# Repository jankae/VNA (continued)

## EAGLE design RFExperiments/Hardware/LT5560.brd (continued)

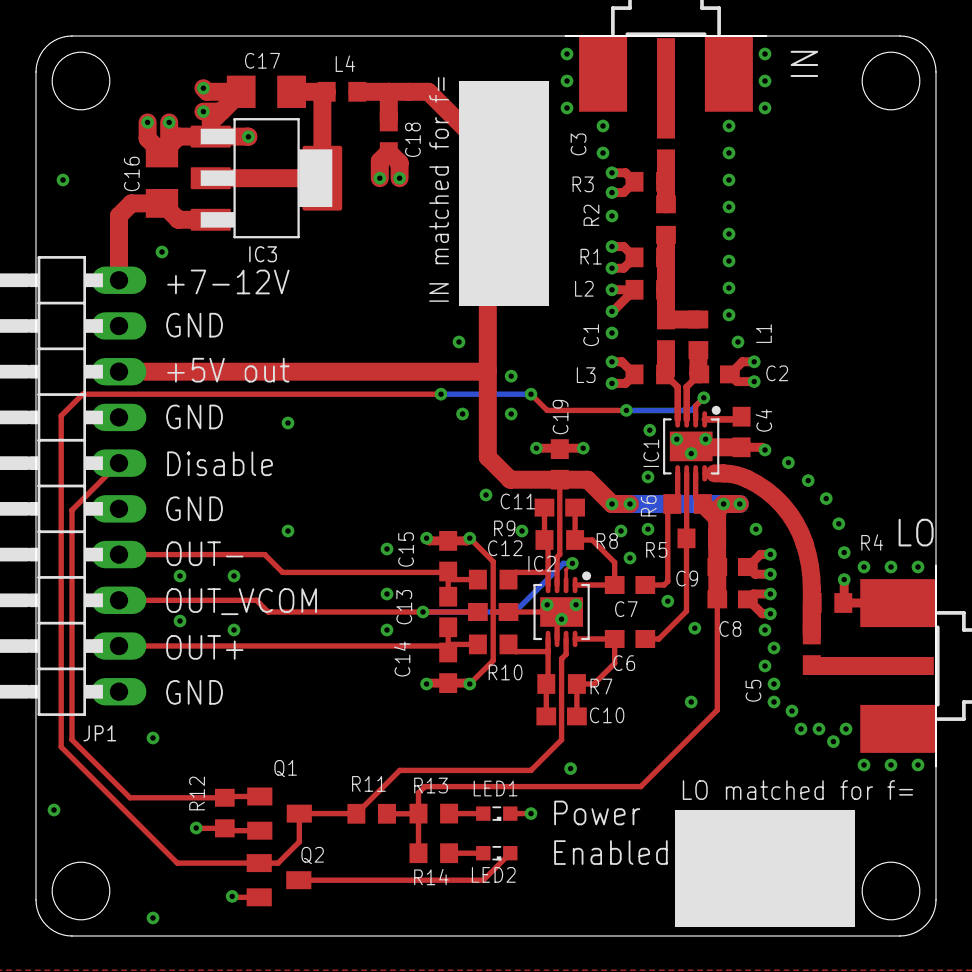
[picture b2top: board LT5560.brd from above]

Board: 2 copper layers, 50.0 x 50.0 mm, 47 parts (0 on the bottom side), 26 nets.

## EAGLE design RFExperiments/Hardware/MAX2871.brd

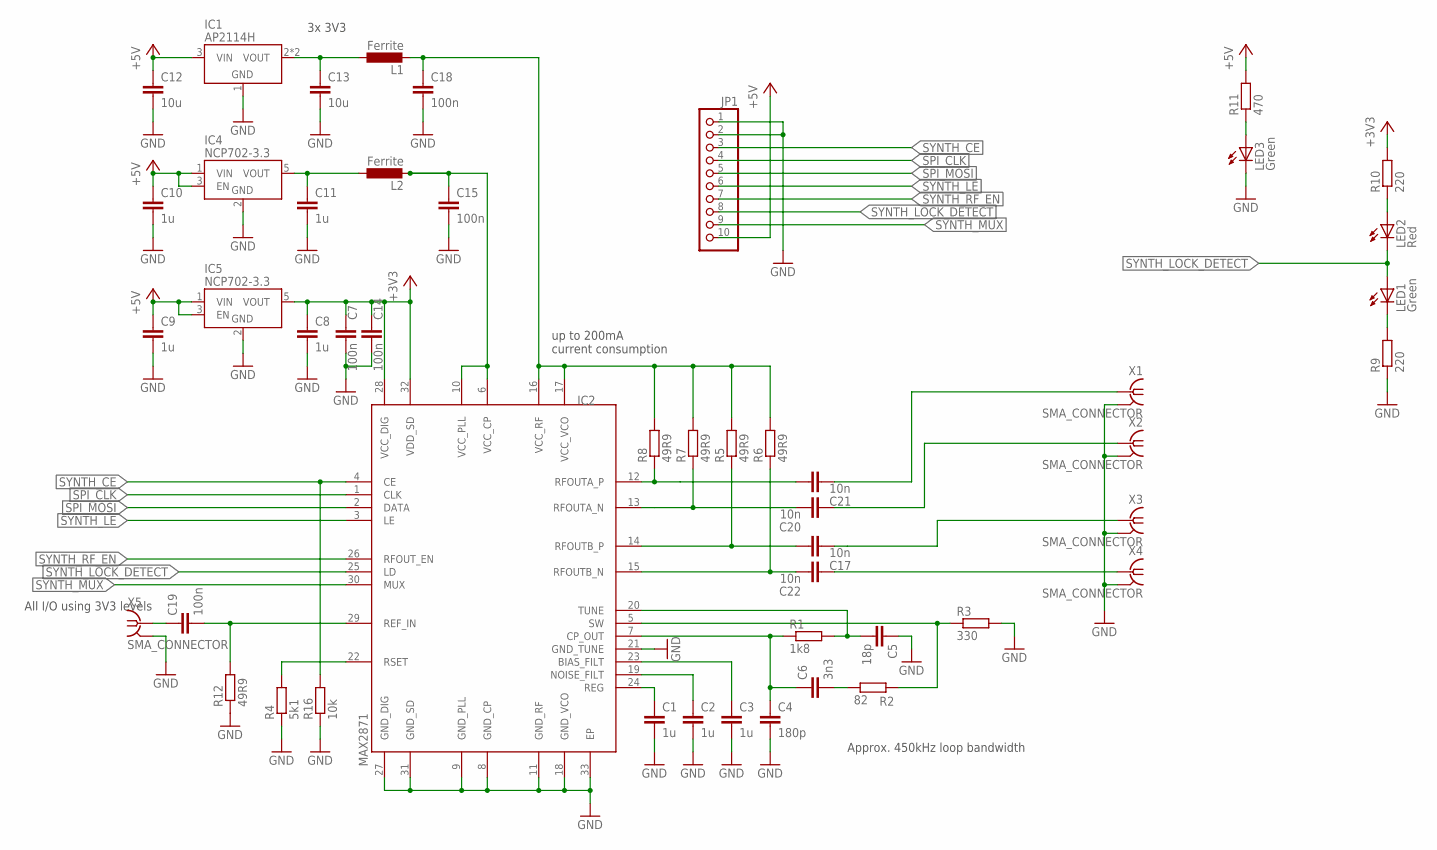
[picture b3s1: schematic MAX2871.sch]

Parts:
C1, C2, C3, C8, C9, C10, C11: 1u; C0603
C4: 180p; C0603
C5: 18p; C0603
C6: 3n3; C0603
C7, C14, C15, C18, C19: 100n; C0603
C12, C13: 10u; C1206
C17, C20, C21, C22: 10n; C0603
IC1: AP2114H; SOT230P700X180-4
IC2: MAX2871; QFN50P500X500X80-33T310
IC4, IC5: NCP702-3.3; SOT95P240X110-5
JP1: PINHD-1X10/90; 1X10/90
L1, L2: Ferrite; R0603
LED1, LED3: Green; LED_SML0603
LED2: Red; LED_SML0603
R1: 1k8; R0603
R2: 82; R0603
R3: 330; R0603
R4: 5k1; R0603
R5, R6, R7, R8, R12: 49R9; R0603
R9, R10: 220; R0603
R11: 470; R0603
R16: 10k; R0603
X1, X2, X3, X4, X5: SMA_CONNECTOR; J502-ND-142-0711-821/826

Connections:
10MHZ_REF: C19.1, X5.1
+3V3: C7.1, C8.1, C14.1, IC2.28 (VCC_DIG), IC2.32 (VDD_SD), IC5.5 (VOUT), R10.2
+5V: C9.1, C10.1, C12.1, IC1.3 (VIN), IC4.1 (VIN), IC4.3 (EN), IC5.1 (VIN), IC5.3 (EN), JP1.10, R11.2
GND: C1.2, C2.2, C3.2, C4.2, C5.1, C7.2, C8.2, C9.2, C10.2, C11.2, C12.2, C13.2, C14.2, C15.2, C18.2, IC1.1 (GND), IC2.8 (GND_CP), IC2.9 (GND_PLL), IC2.11 (GND_RF), IC2.18 (GND_VCO), IC2.21 (GND_TUNE), IC2.27 (GND_DIG), IC2.31 (GND_SD), IC2.33 (EP), IC4.2 (GND), IC5.2 (GND), JP1.1, JP1.2, LED3.C, R3.2, R4.1, R9.1, R12.1, R16.1, X1.G@1 (2), X1.G@2 (2), X1.G@3 (2), X1.G@4 (2), X2.G@1 (2), X2.G@2 (2), X2.G@3 (2), X2.G@4 (2), X3.G@1 (2), X3.G@2 (2), X3.G@3 (2), X3.G@4 (2), X4.G@1 (2), X4.G@2 (2), X4.G@3 (2), X4.G@4 (2), X5.G@1 (2), X5.G@2 (2), X5.G@3 (2), X5.G@4 (2)
unnamed: C5.2, IC2.20 (TUNE), R1.2
unnamed: C4.1, C6.1, IC2.7 (CP_OUT), R1.1
unnamed: C1.1, IC2.24 (REG)
unnamed: C2.1, IC2.19 (NOISE_FILT)
unnamed: C3.1, IC2.23 (BIAS_FILT)
unnamed: C6.2, R2.1
unnamed: IC2.5 (SW), R2.2, R3.1
unnamed: IC2.22 (RSET), R4.2
unnamed: C19.2, IC2.29 (REF_IN), R12.2
unnamed: C18.1, IC2.16 (VCC_RF), IC2.17 (VCC_VCO), L1.2, R5.2, R6.2, R7.2, R8.2
unnamed: C15.1, IC2.6 (VCC_CP), IC2.10 (VCC_PLL), L2.2
unnamed: C22.2, IC2.15 (RFOUTB_N), R6.1
unnamed: LED3.A, R11.1
unnamed: C21.1, IC2.12 (RFOUTA_P), R8.1
unnamed: C20.2, IC2.13 (RFOUTA_N), R7.1
unnamed: C17.1, IC2.14 (RFOUTB_P), R5.1
unnamed: C21.2, X1.1
unnamed: C20.1, X2.1
unnamed: C17.2, X3.1
unnamed: C22.1, X4.1
unnamed: LED1.C, R9.2
unnamed: LED2.A, R10.1
unnamed: C13.1, IC1.2 (VOUT), IC1.4 (VOUT), L1.1
unnamed: C11.1, IC4.5 (VOUT), L2.1
SPI_CLK: IC2.1 (CLK), JP1.4
SPI_MOSI: IC2.2 (DATA), JP1.5
SYNTH_CE: IC2.4 (CE), JP1.3, R16.2
SYNTH_LE: IC2.3 (LE), JP1.6
SYNTH_LOCK_DETECT: IC2.25 (LD), JP1.8, LED1.A, LED2.C
SYNTH_MUX: IC2.30 (MUX), JP1.9
SYNTH_RF_EN: IC2.26 (RFOUT_EN), JP1.7

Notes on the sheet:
up to 200mA current consumption
All I/O using 3V3 levels
3x 3V3
Approx. 450kHz loop bandwidth

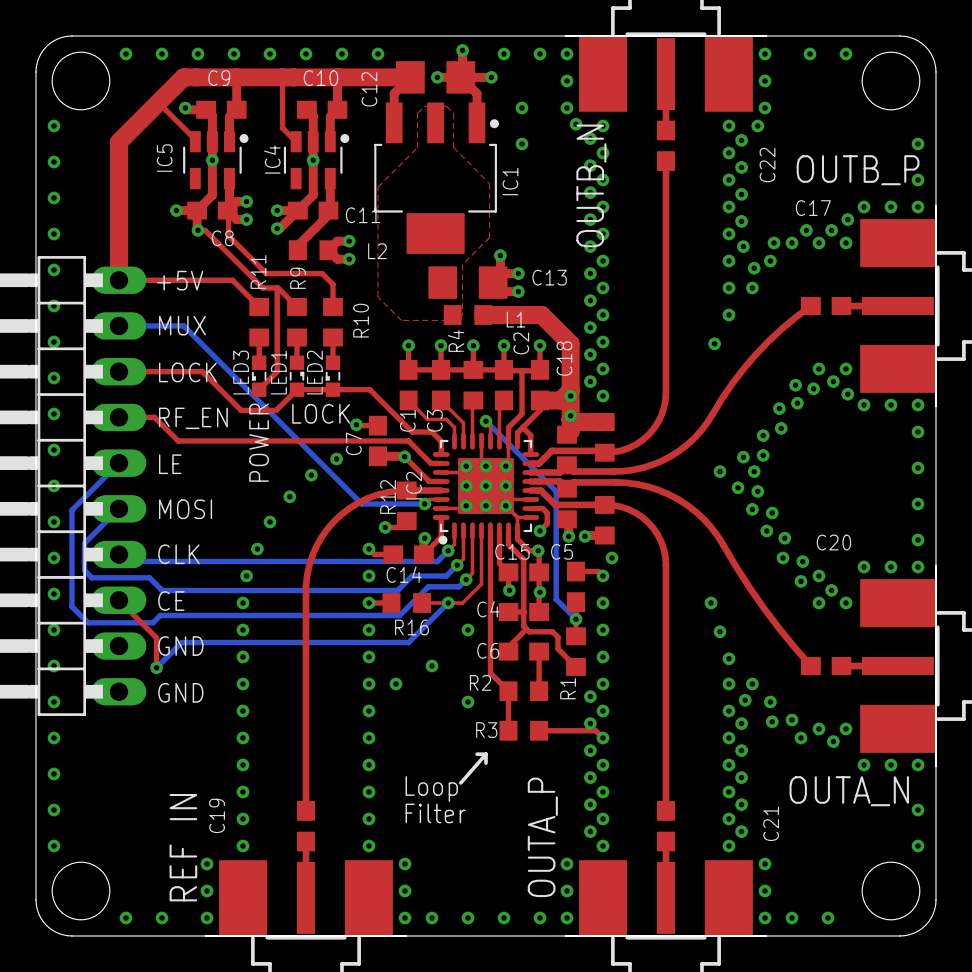
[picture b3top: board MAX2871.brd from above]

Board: 4 copper layers, 50.0 x 50.0 mm, 49 parts (0 on the bottom side), 35 nets.

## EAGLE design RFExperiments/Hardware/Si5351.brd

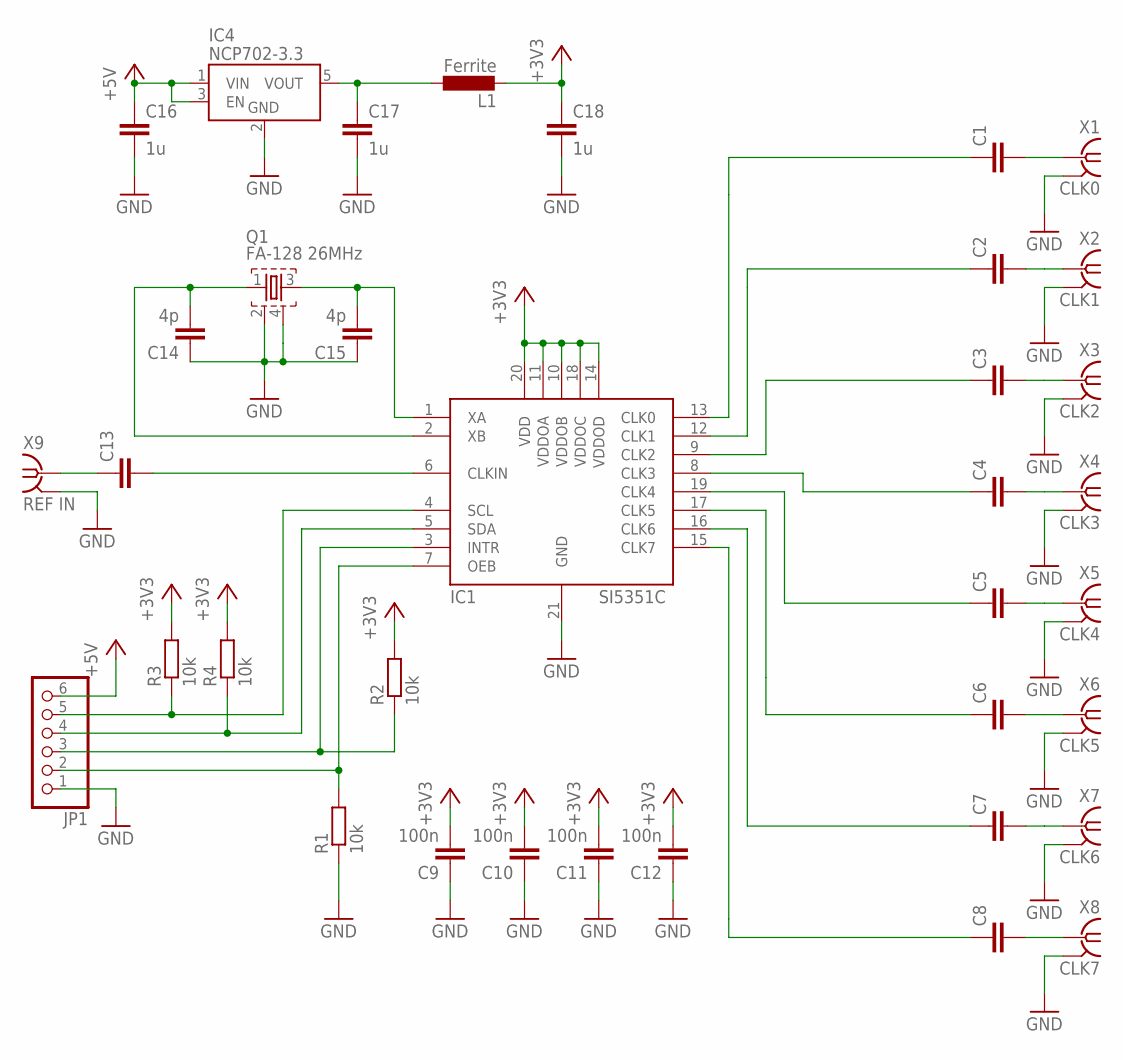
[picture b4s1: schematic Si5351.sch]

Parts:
C1, C2, C3, C4, C5, C6, C7, C8, C13: C-EUC0603; C0603
C9, C10, C11, C12: 100n; C0603
C14, C15: 4p; C0603
C16, C17, C18: 1u; C0603
IC1: SI5351C; QFN50P400X400X90-21T270N
IC4: NCP702-3.3; SOT95P240X110-5
JP1: PINHD-1X6/90; 1X06/90
L1: Ferrite; R0603
Q1: FA-128 26MHz; FA-128
R1, R2, R3, R4: 10k; R0603
X1: CLK0; J502-ND-142-0711-821/826
X2: CLK1; J502-ND-142-0711-821/826
X3: CLK2; J502-ND-142-0711-821/826
X4: CLK3; J502-ND-142-0711-821/826
X5: CLK4; J502-ND-142-0711-821/826
X6: CLK5; J502-ND-142-0711-821/826
X7: CLK6; J502-ND-142-0711-821/826
X8: CLK7; J502-ND-142-0711-821/826
X9: REF IN; J502-ND-142-0711-821/826

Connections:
+3V3: C9.2, C10.2, C11.2, C12.2, C18.1, IC1.10 (VDDOB), IC1.11 (VDDOA), IC1.14 (VDDOD), IC1.18 (VDDOC), IC1.20 (VDD), L1.2, R2.2, R3.2, R4.2
+5V: C16.1, IC4.1 (VIN), IC4.3 (EN), JP1.6
GND: C9.1, C10.1, C11.1, C12.1, C14.1, C15.1, C16.2, C17.2, C18.2, IC1.21 (GND), IC4.2 (GND), JP1.1, Q1.2, Q1.4, R1.1, X1.G@1 (2), X1.G@2 (2), X1.G@3 (2), X1.G@4 (2), X2.G@1 (2), X2.G@2 (2), X2.G@3 (2), X2.G@4 (2), X3.G@1 (2), X3.G@2 (2), X3.G@3 (2), X3.G@4 (2), X4.G@1 (2), X4.G@2 (2), X4.G@3 (2), X4.G@4 (2), X5.G@1 (2), X5.G@2 (2), X5.G@3 (2), X5.G@4 (2), X6.G@1 (2), X6.G@2 (2), X6.G@3 (2), X6.G@4 (2), X7.G@1 (2), X7.G@2 (2), X7.G@3 (2), X7.G@4 (2), X8.G@1 (2), X8.G@2 (2), X8.G@3 (2), X8.G@4 (2), X9.G@1 (2), X9.G@2 (2), X9.G@3 (2), X9.G@4 (2)
unnamed: C1.2, X1.1
unnamed: C2.2, X2.1
unnamed: C3.2, X3.1
unnamed: C4.2, X4.1
unnamed: C5.2, X5.1
unnamed: C6.2, X6.1
unnamed: C7.2, X7.1
unnamed: C8.2, X8.1
unnamed: C1.1, IC1.13 (CLK0)
unnamed: C2.1, IC1.12 (CLK1)
unnamed: C3.1, IC1.9 (CLK2)
unnamed: C8.1, IC1.15 (CLK7)
unnamed: C7.1, IC1.16 (CLK6)
unnamed: C6.1, IC1.17 (CLK5)
unnamed: C5.1, IC1.19 (CLK4)
unnamed: C4.1, IC1.8 (CLK3)
unnamed: IC1.4 (SCL), JP1.5, R3.1
unnamed: C13.1, X9.1
unnamed: C13.2, IC1.6 (CLKIN)
unnamed: IC1.5 (SDA), JP1.4, R4.1
unnamed: IC1.3 (INTR), JP1.3, R2.1
unnamed: IC1.7 (OEB), JP1.2, R1.2
unnamed: C15.2, IC1.1 (XA), Q1.3
unnamed: C14.2, IC1.2 (XB), Q1.1
unnamed: C17.1, IC4.5 (VOUT), L1.1

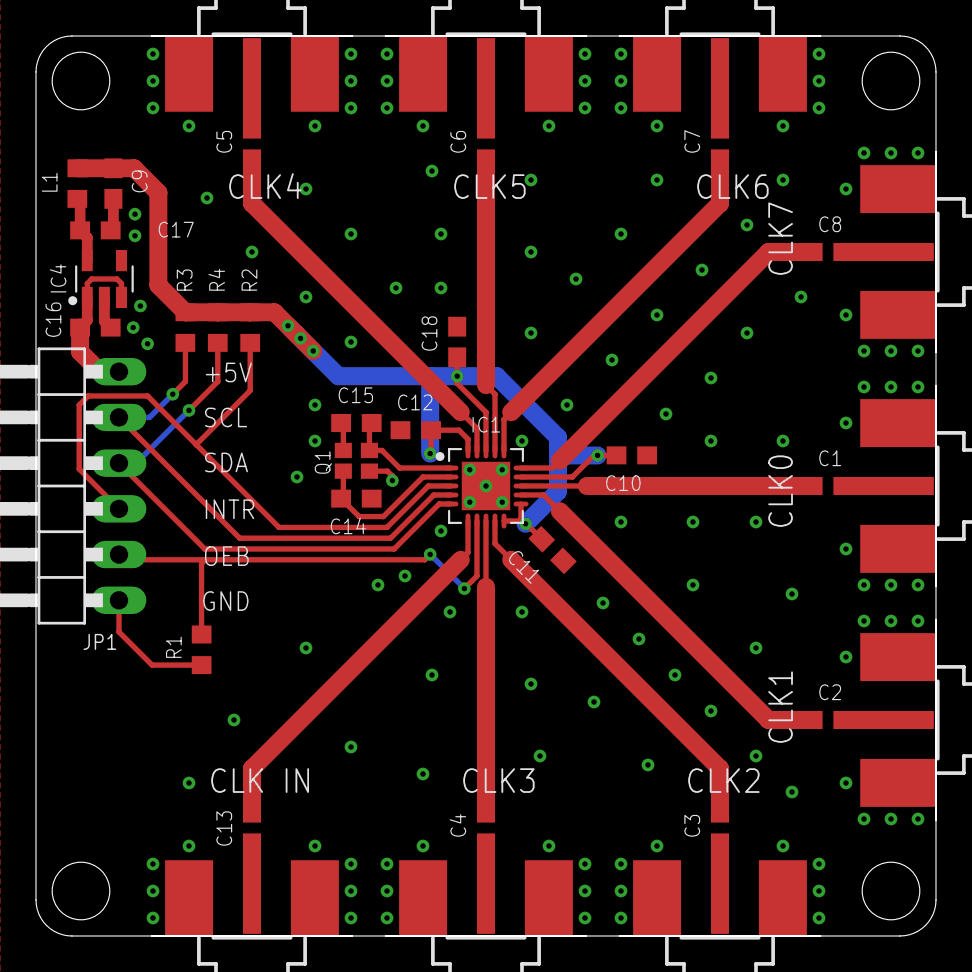
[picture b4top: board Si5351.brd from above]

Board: 2 copper layers, 50.0 x 50.0 mm, 36 parts (0 on the bottom side), 28 nets.

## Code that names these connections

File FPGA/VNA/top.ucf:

CONFIG VCCAUX  = 3.3;
NET "CLK" PERIOD = 62.5 ns;


NET "ATTENUATION[6]" IOSTANDARD = LVCMOS33;
NET "ATTENUATION[5]" IOSTANDARD = LVCMOS33;
NET "ATTENUATION[4]" IOSTANDARD = LVCMOS33;
NET "ATTENUATION[3]" IOSTANDARD = LVCMOS33;
NET "ATTENUATION[2]" IOSTANDARD = LVCMOS33;
NET "ATTENUATION[1]" IOSTANDARD = LVCMOS33;
NET "ATTENUATION[0]" IOSTANDARD = LVCMOS33;


NET "ATTENUATION[6]" LOC = P26;
NET "ATTENUATION[5]" LOC = P27;
NET "ATTENUATION[4]" LOC = P29;
NET "ATTENUATION[3]" LOC = P30;
NET "ATTENUATION[2]" LOC = P32;
NET "ATTENUATION[1]" LOC = P33;
NET "ATTENUATION[0]" LOC = P34;


NET "LEDS[7]" IOSTANDARD = LVCMOS33;
NET "LEDS[6]" IOSTANDARD = LVCMOS33;
NET "LEDS[5]" IOSTANDARD = LVCMOS33;
NET "LEDS[4]" IOSTANDARD = LVCMOS33;
NET "LEDS[3]" IOSTANDARD = LVCMOS33;
NET "LEDS[2]" IOSTANDARD = LVCMOS33;
NET "LEDS[1]" IOSTANDARD = LVCMOS33;
NET "LEDS[0]" IOSTANDARD = LVCMOS33;


NET "LEDS[7]" LOC = P105;
NET "LEDS[6]" LOC = P104;
NET "LEDS[5]" LOC = P99;
NET "LEDS[4]" LOC = P94;
NET "LEDS[3]" LOC = P85;
NET "LEDS[2]" LOC = P82;
NET "LEDS[1]" LOC = P75;
NET "LEDS[0]" LOC = P118;


NET "AMP_PWDN" IOSTANDARD = LVCMOS33;
NET "BAND_SELECT" IOSTANDARD = LVCMOS33;
NET "CLK" IOSTANDARD = LVCMOS33;
NET "FILT_IN_C2" IOSTANDARD = LVCMOS33;
NET "FILT_IN_C1" IOSTANDARD = LVCMOS33;
NET "FILT_OUT_C2" IOSTANDARD = LVCMOS33;
NET "FILT_OUT_C1" IOSTANDARD = LVCMOS33;
NET "LO1_CE" IOSTANDARD = LVCMOS33;
NET "LO1_LD" IOSTANDARD = LVCMOS33;
NET "LO1_LE" IOSTANDARD = LVCMOS33;
NET "LO1_CLK" IOSTANDARD = LVCMOS33;
NET "LO1_MOSI" IOSTANDARD = LVCMOS33;
NET "LO1_MUX" IOSTANDARD = LVCMOS33;
NET "MCU_AUX1" IOSTANDARD = LVCMOS33;
NET "LO1_RF_EN" IOSTANDARD = LVCMOS33;
NET "SOURCE_RF_EN" IOSTANDARD = LVCMOS33;
NET "SOURCE_MUX" IOSTANDARD = LVCMOS33;
NET "SOURCE_LE" IOSTANDARD = LVCMOS33;
NET "SOURCE_MOSI" IOSTANDARD = LVCMOS33;
NET "SOURCE_LD" IOSTANDARD = LVCMOS33;
NET "SOURCE_CLK" IOSTANDARD = LVCMOS33;
NET "SOURCE_CE" IOSTANDARD = LVCMOS33;
NET "SDA" IOSTANDARD = LVCMOS33;
NET "SCL" IOSTANDARD = LVCMOS33;
NET "RESET" IOSTANDARD = LVCMOS33;
NET "REF_SDO" IOSTANDARD = LVCMOS33;
NET "REF_SCLK" IOSTANDARD = LVCMOS33;
NET "REF_MIX_EN" IOSTANDARD = LVCMOS33;
NET "PORT_SELECT" IOSTANDARD = LVCMOS33;
NET "REF_CONVSTART" IOSTANDARD = LVCMOS33;
NET "PORT2_SDO" IOSTANDARD = LVCMOS33;
NET "PORT2_SCLK" IOSTANDARD = LVCMOS33;
NET "PORT2_CONVSTART" IOSTANDARD = LVCMOS33;
NET "PORT2_MIX_EN" IOSTANDARD = LVCMOS33;
NET "PORT1_SDO" IOSTANDARD = LVCMOS33;
NET "PORT1_SCLK" IOSTANDARD = LVCMOS33;
NET "PORT1_MIX_EN" IOSTANDARD = LVCMOS33;
NET "PORT1_CONVSTART" IOSTANDARD = LVCMOS33;
NET "MCU_SCK" IOSTANDARD = LVCMOS33;
NET "MCU_NSS" IOSTANDARD = LVCMOS33;
NET "MCU_MISO" IOSTANDARD = LVCMOS33;
NET "MCU_MOSI" IOSTANDARD = LVCMOS33;
NET "MCU_INTR" IOSTANDARD = LVCMOS33;
NET "MCU_AUX2" IOSTANDARD = LVCMOS33;
NET "MCU_AUX3" IOSTANDARD = LVCMOS33;


NET "AMP_PWDN" LOC = P24;
NET "BAND_SELECT" LOC = P22;
NET "CLK" LOC = P14;
NET "FILT_IN_C1" LOC = P15;
NET "FILT_IN_C2" LOC = P16;
NET "FILT_OUT_C1" LOC = P21;
NET "FILT_OUT_C2" LOC = P17;
NET "LO1_CE" LOC = P138;
NET "LO1_CLK" LOC = P141;
NET "LO1_LD" LOC = P142;
NET "LO1_LE" LOC = P139;
NET "LO1_MOSI" LOC = P140;
NET "LO1_MUX" LOC = P144;
NET "LO1_RF_EN" LOC = P143;
NET "MCU_AUX1" LOC = P55;
NET "MCU_AUX2" LOC = P51;
NET "MCU_AUX3" LOC = P50;
NET "MCU_INTR" LOC = P57;
NET "MCU_MISO" LOC = P61;
NET "MCU_MOSI" LOC = P59;
NET "MCU_NSS" LOC = P58;
NET "MCU_SCK" LOC = P56;
NET "PORT1_CONVSTART" LOC = P134;
NET "PORT1_MIX_EN" LOC = P137;
NET "PORT1_SCLK" LOC = P132;
NET "PORT1_SDO" LOC = P133;
NET "PORT_SELECT" LOC = P23;
NET "PORT2_CONVSTART" LOC = P47;
NET "PORT2_MIX_EN" LOC = P44;
NET "PORT2_SCLK" LOC = P45;
NET "PORT2_SDO" LOC = P46;
NET "REF_CONVSTART" LOC = P43;
NET "REF_SCLK" LOC = P40;
NET "REF_SDO" LOC = P41;
NET "REF_MIX_EN" LOC = P35;
NET "RESET" LOC = P48;
NET "SCL" LOC = P6;
NET "SDA" LOC = P9;
NET "SOURCE_CE" LOC = P1;
NET "SOURCE_CLK" LOC = P7;
NET "SOURCE_LD" LOC = P10;
NET "SOURCE_LE" LOC = P2;
NET "SOURCE_MOSI" LOC = P5;
NET "SOURCE_MUX" LOC = P8;
NET "SOURCE_RF_EN" LOC = P11;

# PlanAhead Generated IO constraints 

NET "PORT1_SCLK" SLEW = FAST;
NET "PORT2_SCLK" SLEW = FAST;
NET "REF_SCLK" SLEW = FAST;

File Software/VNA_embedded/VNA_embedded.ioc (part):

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Mcu.Name=STM32L432K(B-C)Ux
Mcu.Package=UFQFPN32
Mcu.UserName=STM32L432KCUx
PA0.GPIOParameters=GPIO_Speed,GPIO_Label
PA0.GPIO_Label=FPGA_AUX3
PA0.GPIO_Speed=GPIO_SPEED_FREQ_VERY_HIGH
PA0.Signal=GPIO_Output
PA1.GPIOParameters=GPIO_Speed,GPIO_Label
PA1.GPIO_Label=FPGA_RESET
PA1.GPIO_Speed=GPIO_SPEED_FREQ_VERY_HIGH
PA1.Signal=GPIO_Output
PA10.Mode=I2C
PA10.Signal=I2C1_SDA
PA11.Mode=Device
PA11.Signal=USB_DM
PA12.Mode=Device
PA12.Signal=USB_DP
PA13\ (JTMS-SWDIO).Mode=Serial_Wire
PA13\ (JTMS-SWDIO).Signal=SYS_JTMS-SWDIO
PA14\ (JTCK-SWCLK).Mode=Serial_Wire
PA14\ (JTCK-SWCLK).Signal=SYS_JTCK-SWCLK
PA15\ (JTDI).GPIOParameters=GPIO_Label
PA15\ (JTDI).GPIO_Label=USB_EN
PA15\ (JTDI).Signal=GPIO_Output
PA2.Mode=Half_duplex(single_wire_mode)
PA2.Signal=USART2_TX
PA9.Mode=I2C
PA9.Signal=I2C1_SCL
PB3\ (JTDO-TRACESWO).Mode=Full_Duplex_Master
PB3\ (JTDO-TRACESWO).Signal=SPI3_SCK
PB4\ (NJTRST).Mode=Full_Duplex_Master
PB4\ (NJTRST).Signal=SPI3_MISO
PB5.Mode=Full_Duplex_Master
PB5.Signal=SPI3_MOSI
PB6.GPIOParameters=GPIO_Speed,GPIO_Label
PB6.GPIO_Label=FPGA_CS
PB6.GPIO_Speed=GPIO_SPEED_FREQ_VERY_HIGH
PB6.Signal=GPIO_Output
PB7.GPIOParameters=GPIO_Label
PB7.GPIO_Label=FPGA_INTR
PB7.Signal=GPIO_Input
PC14-OSC32_IN\ (PC14).GPIOParameters=GPIO_Label
PC14-OSC32_IN\ (PC14).GPIO_Label=FPGA_AUX1
PC14-OSC32_IN\ (PC14).Signal=GPIO_Output
PC15-OSC32_OUT\ (PC15).GPIOParameters=GPIO_Label
PC15-OSC32_OUT\ (PC15).GPIO_Label=FPGA_AUX2
PC15-OSC32_OUT\ (PC15).Signal=GPIO_Output
RCC.HSE_VALUE=8000000
RCC.SYSCLKFreq_VALUE=80000000
RCC.SYSCLKSource=RCC_SYSCLKSOURCE_PLLCLK
board=custom

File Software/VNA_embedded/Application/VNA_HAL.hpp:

#pragma once

#include "stm.hpp"
#include "Si5351C.hpp"
#include "max2871.hpp"
#include "main.h"

extern I2C_HandleTypeDef hi2c1;
extern SPI_HandleTypeDef hspi3;

namespace VNAHAL {

static Si5351C Si5351 = Si5351C(&hi2c1, 26000000);
static MAX2871 Source = MAX2871(&hspi3, FPGA_CS_GPIO_Port, FPGA_CS_Pin, nullptr, 0, nullptr, 0, nullptr, 0, GPIOB, GPIO_PIN_4);
static MAX2871 LO1 = MAX2871(&hspi3, FPGA_CS_GPIO_Port, FPGA_CS_Pin, nullptr, 0, nullptr, 0, nullptr, 0, GPIOB, GPIO_PIN_4);

// Mapping of the Si5351 channels to PLLs/Mixers
namespace SiChannel {
	enum {
		Source = 3,
		LO1 = 2,
		Port2LO2 = 1,
		RefLO2 = 5,
		Port1LO2 = 4,
		LowbandSource = 0,
		ReferenceOut = 6,
		FPGA = 7,
	};
}

}

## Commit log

2020-04-02 Synthesizer and first mixer board
2020-04-02 Si5351C clock distributor board
2020-04-02 Second mixer/ADC driver board
2020-04-10 Gerber and BOM
2020-04-10 CubeMX Project with SI5351 driver
2020-04-11 Minimum VNA signal flow implemented
2020-04-12 USB CDC + ADC timer trigger bugfix
2020-04-12 Transmission of sweep settings and measurement results via USB
2020-04-12 Device driver on PC side
2020-04-13 Minimalistic GUI for display of S-parameters
2020-04-13 Custom value input dialog
2020-04-15 Central data model, selectable traces for plots, fullscreen plot, buttons for frequency/span changes
2020-04-16 Settings for points/averages added to toolbar
2020-04-16 QChart -> QWT (speed improvement)
2020-04-17 OSLT calibration mathe
2020-04-20 Controls changed from toolbar to custom menu
2020-04-20 Delays removed for speed test
2020-04-23 Bugfixes and tests
2020-04-24 Working S11 measurement and simple calibration menu
2020-04-25 ADCs sampling continuouly (gets rid of frequent phase jumps due to timer divider, still some phase creapage
2020-04-25 Improved frequency accuracy when selecting Si5351 dividers, phase creapage eliminated
2020-04-26 More ADC samples per signal period, full two-port operation
2020-04-27 1.IF moved (fixed random error on PLL relock, probably due to leakage)
2020-04-28 Queued connection for datapoint transfer, calibration with progress dialog
2020-04-28 Functioning menu entries for full calibration, sweep speed improved
2020-04-30 Partial schematic + Layout
2020-04-30 Placing
2020-05-01 Partial routing
2020-05-01 Routing
2020-05-03 Shield outline and small layout fixes
2020-05-03 Mixers disabled by default, GND plane cutouts under high-speed component pads
2020-05-03 Silkscreen
2020-05-03 Testpoints + Gerber
2020-05-05 BOM + AUX4->RESET
2020-05-05 MCP33131/SPI command driver
2020-05-05 CubeMX generated code
2020-05-06 Sweep and sampling logic
2020-05-07 BOM adjustments
2020-05-07 FPGA features completed
2020-05-07 Bugfixes SPI commands
2020-05-08 Tests/bugfixes
2020-05-08 FPGA protocol description
2020-05-08 uC Software adapted from RFExperiments
2020-05-09 Save/load calibration to file
2020-05-10 Sync signal for switching regulator implemented
2020-05-10 Piecewise curve plotting, timestamp on calibration data
2020-05-10 Status panel + bugfixes
2020-05-11 Averaging across multiple sweeps
2020-05-11 Fix phase align issue for 2.LO
2020-05-12 Various minor improvements and bugfixes/workarounds for HW mistakes
2020-05-13 Bugfixes
2020-05-14 ADC SPI frequency reduced + further bugfixes
2020-05-14 Workaround for spurious freezing sampling module (needs proper fix)
2020-05-15 SPI CS high reload bug fixed, MCP33131 rewritten as statemachine
2020-05-15 Sampling rewritten as FSM, inputs synchronized
2020-05-16 Added temperature measurement for PLLs
2020-05-26 ADC min/max, support for sweep halt/resume before sampling each point
2020-05-26 Part values of final IF filter adjusted
2020-05-28 Lowband source implemented, faster algorithm for PLL divider selection
2020-05-29 Calibration kit configuration dialog and its coefficients taken into account during calibration
2020-05-30 Fixed calculation mistakes in calibration kit routines
2020-05-31 touchstone and calibration kit measurement support
2020-06-02 Menu GUI improved
2020-06-04 Bugfixes in calibration + preparations for different traces
2020-06-05 Manual control mode
2020-06-08 Trace dialog/widget completed
2020-06-09 Smithchart for traces
2020-06-12 Source level control implemented
2020-06-13 Bodeplot implemented with trace model
2020-06-13 Bugfixes: Min/max hold, color and visibility changes in bodeplot
2020-06-14 Import touchstone to traces
2020-06-15 Bugfixes trace import/edit
2020-06-15 Plots organized in tiles: resizing/splitting
2020-06-15 Bugfixes tile merging
2020-06-15 Plot update rate limited
2020-06-16 Pictures
2020-06-16 Screenshots
2020-06-17 Touchstone/Trace export
2020-06-20 Marker table
2020-06-20 Marker displayed in plots
2020-06-21 Drag markers on bodeplot
2020-06-21 Drag markers on smithchart
2020-06-22 Impedance matching dialog
2020-06-23 Impedance matching schematic images + two Cs/Ls bugfixes
2020-06-23 RF block diagram
2020-06-24 Isolation shielding data
2020-06-24 Fixed averaging for trace model
2020-06-25 .svg blockdiagram
2020-06-25 PCB markings
2020-06-25 Shielding milling picture
2020-06-25 updated screenshot
2020-06-25 Bugfix calkit dialog/screenshot antenna
2020-07-06 Add calibration coefficients as traces, update plots if marker changed while data constant
2020-07-16 Create LICENSE
2020-08-06 Support for calibration kit measurements (untested)
2020-08-06 Improved device handling, preparations for differentiating between multiple connected devices
2020-08-08 GUI bugfixes and partial menu/toolbar creation
2020-08-08 Hide markers on bodeplot if trace is invisible
2020-08-08 Auto/manual bodeplot axis scale
2020-08-08 Device info in statusbar
2020-08-09 Calibration toolbar/menu/dialog + general bugfixes
2020-08-12 removed boost dependency, fixed compilation on windows
2020-08-12 Preparations for loading/saving calibration trace data
2020-08-12 Measurements + top cover layout
2020-08-13 CubeMX CDC driver adjusted to custom class
2020-08-13 Cleanup of not needed CDC code
2020-08-13 Device log accessable via additional USB endpoint
2020-08-14 device code cleanup
2020-08-14 Fix deadlock on device disconnect on windows/minGW
2020-08-14 improved encoding/decoding of protocol packets
2020-08-14 Fixed compiler warnings
2020-08-14 Calibration trace data save/open
2020-08-16 Calibration kit stored with calibration traces
2020-08-16 Device specific default calibration + minor bugfixes
2020-08-16 dedicated trace import dialog, touchstone import moved to traceWidget
2020-08-24 CAD files for aluminium cover
2020-09-11 Unified central software components to work with next hardware revision
2020-09-12 Reference control added
2020-09-14 SweepConfig format changed to allow different settling times and samples for every point
